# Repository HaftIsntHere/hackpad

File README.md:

# Hackpad
My hackpad includes 4 keys, a knob and an oled screen
## Why I made this
I made a hackpad because I always wanted to make my own DIY hardware, and I saw hackpad is coming back so it was a good chance to get into that category.
**Thank you to the Hackpad team, the Highway to Undercity team and HackClub for making this possible!**
 <br>
## Schematic
 <br>
## PCB
 <br>
## Case
 <br>
> Everything fits together using 4 m3 screws and bolts
## BOM
- 1 XIAO RP2040
- 1 OLED Screen 128x32 SSD1306
- 1 Rotary Encoder
- 4 [Akko V3 Creamy Blue](https://www.amazon.com/gp/product/B0C3H7PR1Z) switches
- 2 SK6812 LEDs

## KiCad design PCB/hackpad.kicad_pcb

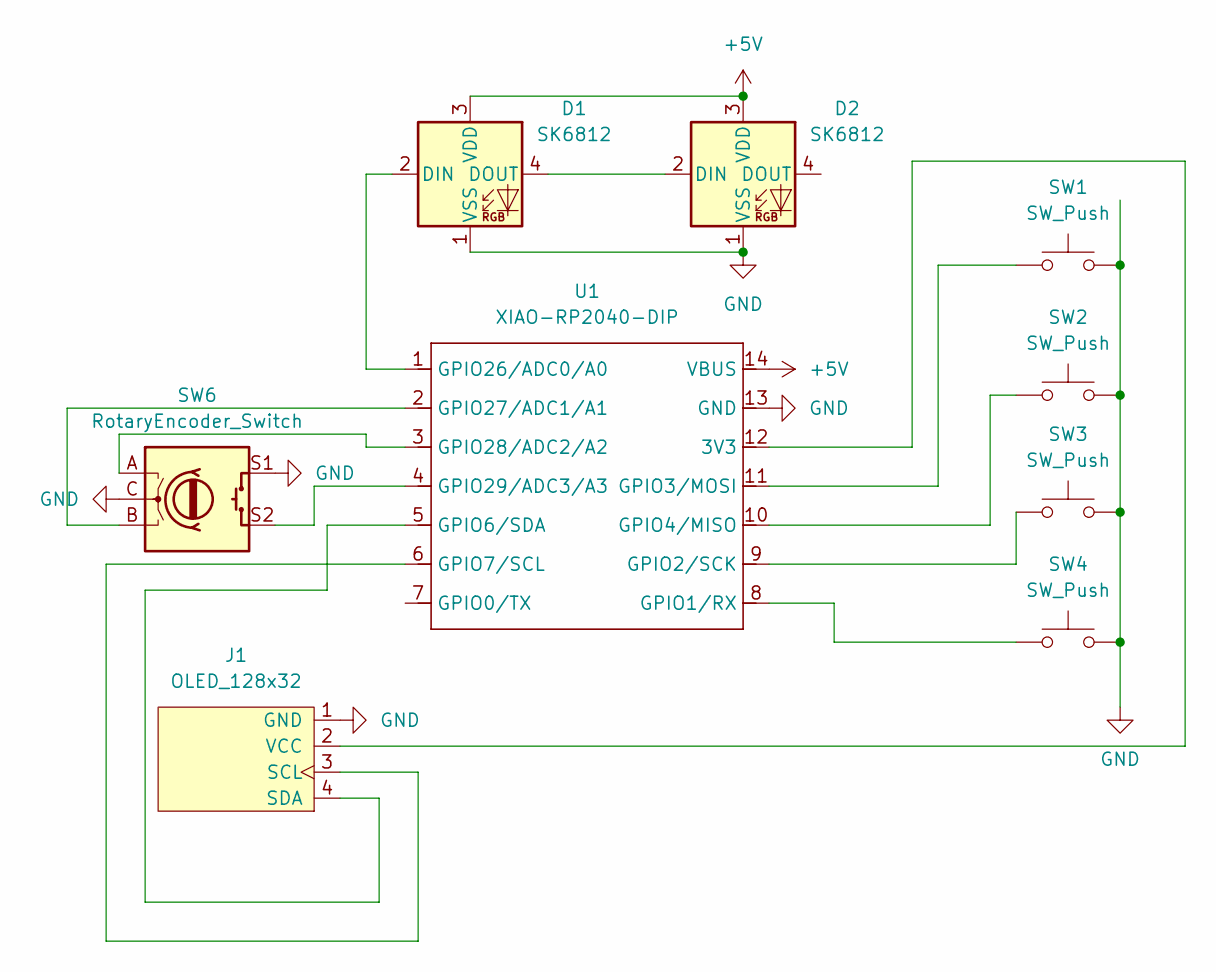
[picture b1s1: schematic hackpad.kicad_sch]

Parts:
D1, D2: SK6812; LED_SK6812MINI_PLCC4_3.5x3.5mm_P1.75mm
J1: OLED_128x32
SW1, SW2, SW3, SW4: SW_Push; SW_Cherry_MX_1.00u_PCB
SW6: RotaryEncoder_Switch; RotaryEncoder_Alps_EC11E-Switch_Vertical_H20mm
U1: XIAO-RP2040-DIP

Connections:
+5V: D1.3 (VDD), D2.3 (VDD), U1.14 (VBUS)
GND: D1.1 (VSS), D2.1 (VSS), J1.1 (GND), SW1.1, SW2.1, SW3.1, SW4.1, SW6.C, SW6.S1, U1.13 (GND)
unnamed: D1.2 (DIN), U1.1 (GPIO26/ADC0/A0)
unnamed: D1.4 (DOUT), D2.2 (DIN)
unnamed: J1.3 (SCL), U1.6 (GPIO7/SCL)
unnamed: J1.4 (SDA), U1.5 (GPIO6/SDA)
unnamed: J1.2 (VCC), U1.12 (3V3)
unnamed: SW4.2, U1.8 (GPIO1/RX)
unnamed: SW3.2, U1.9 (GPIO2/SCK)
unnamed: SW1.2, U1.11 (GPIO3/MOSI)
unnamed: SW2.2, U1.10 (GPIO4/MISO)
unnamed: SW6.B, U1.2 (GPIO27/ADC1/A1)
unnamed: SW6.A, U1.3 (GPIO28/ADC2/A2)
unnamed: SW6.S2, U1.4 (GPIO29/ADC3/A3)

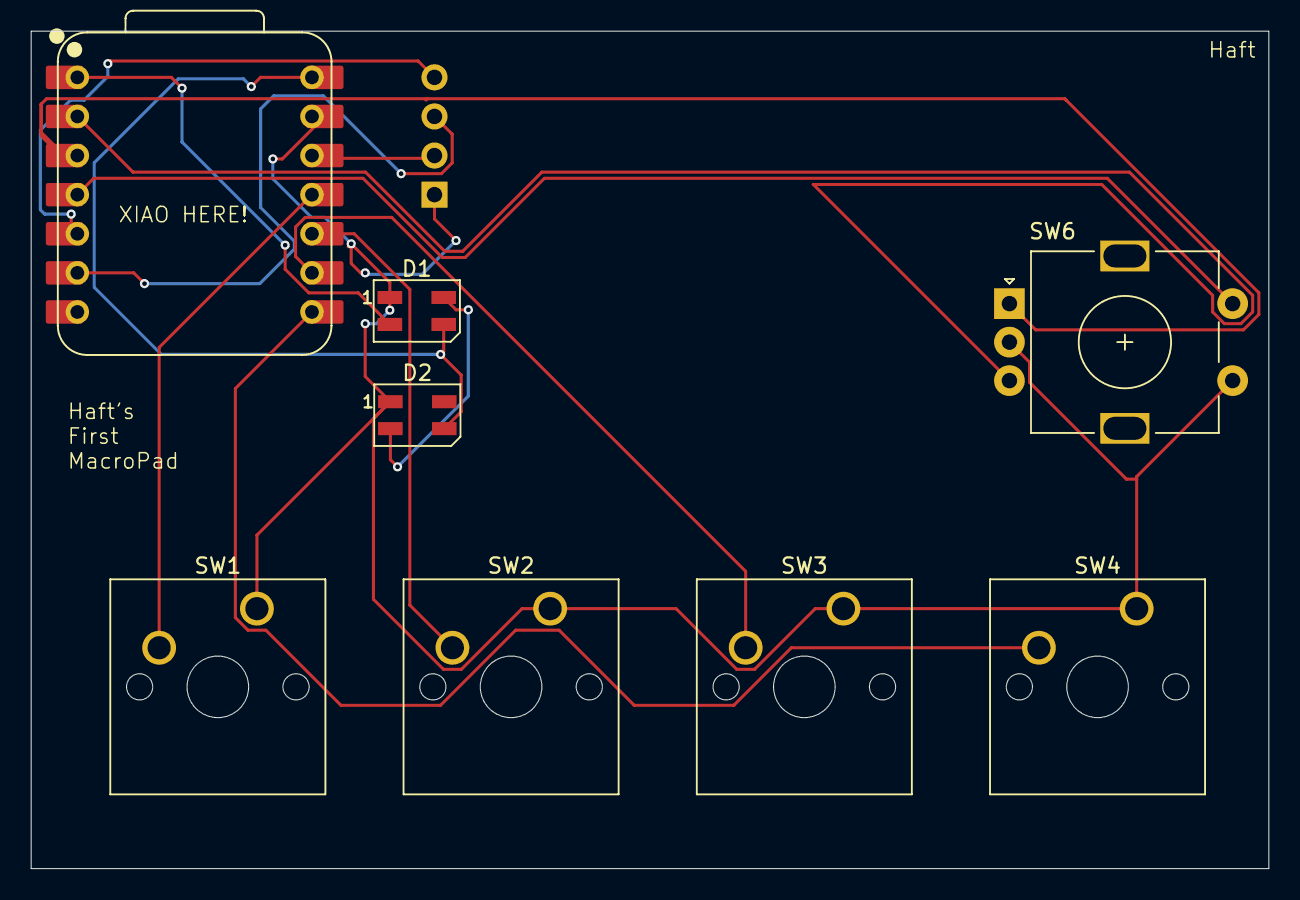
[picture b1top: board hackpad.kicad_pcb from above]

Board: 2 copper layers, 80.4 x 54.4 mm, 9 parts (0 on the bottom side), 14 nets.

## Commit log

2025-06-13 Add my hackpad
2025-06-13 readme fix
